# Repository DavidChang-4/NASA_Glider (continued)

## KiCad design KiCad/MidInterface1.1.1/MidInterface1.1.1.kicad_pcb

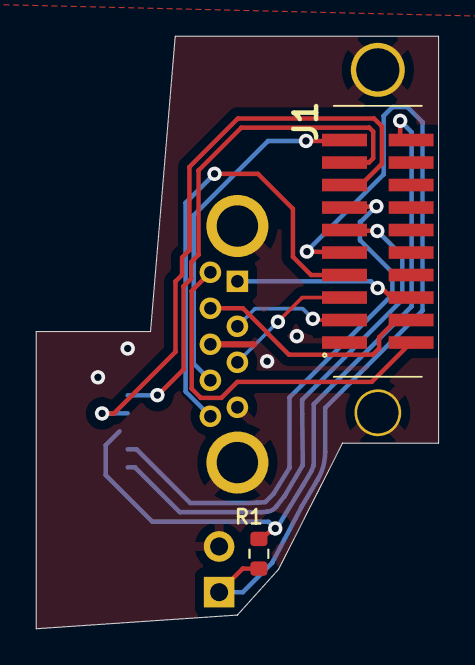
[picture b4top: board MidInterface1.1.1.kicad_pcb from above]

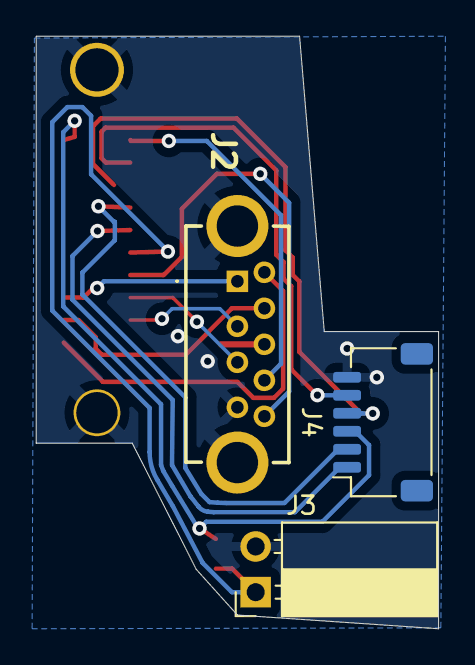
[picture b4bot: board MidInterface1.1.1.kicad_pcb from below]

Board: 2 copper layers, 22.4 x 32.9 mm, 7 parts (3 on the bottom side), 14 nets.

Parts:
H1, H2: (no value)
J1: G125-FS12005L0P
J2: SS-52000-004; SS52000004
J3: Screw_Terminal_01x02; PinSocket_1x02_P2.54mm_Horizontal
J4: Conn_01x06; JST_SH_SM06B-SRSS-TB_1x06-1MP_P1.00mm_Horizontal
R1: 10k; R_0603_1608Metric

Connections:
+3.3V: J1.20, J4.3, R1.2
+5V: J1.4, J2.5 (SSRX-)
+BATT: J1.10, J2.6 (SSRX+)
/CAN-H: J1.12, J2.8 (SSTX-)
/CAN-L: J1.11, J2.9 (SSTX+)
/Encoder A: J1.8, J4.4
/Encoder B: J1.9, J4.5
/Limit Switch: J1.5, J3.1, R1.1
/M+: J1.6, J4.1
/M-: J1.7, J4.2
/USB D+: J1.3, J2.3 (D+)
/USB D-: J1.2, J2.2 (D-)
GND: H1.11, H2.11, J1.1, J2.4 (GND), J2.7 (GND_DRAIN), J2.MH1, J2.MH2, J3.2, J4.6
VBUS: J1.13, J2.1 (VBUS)

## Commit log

2024-07-16 Add all kicad files from MAE drive
